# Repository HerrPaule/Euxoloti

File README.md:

# Euxoloti
Euxoloti is a project to use the great Axoloti core in the world of Eurorack. 

The project is fully open and released under CC-BY-SA-NC

Further deatils about functions and order, check http://irieelectronics.de/euxoloti
and the Axoloti Forum: http://community.axoloti.com/t/euxoloti-for-axoloti-eurorack-module/

A great detailed build step by step instruction by FMA from the Axoloti Forum (work in progress): https://docs.google.com/document/d/1Rx9O_k-dUJQDzONVk0AzewmyFckbQyXHiNsPy8fmUj8/edit

AXOLOTI: http://axoloti.be
<br>
Book about the Axoloti: https://leanpub.com/getting-started-with-axoloti

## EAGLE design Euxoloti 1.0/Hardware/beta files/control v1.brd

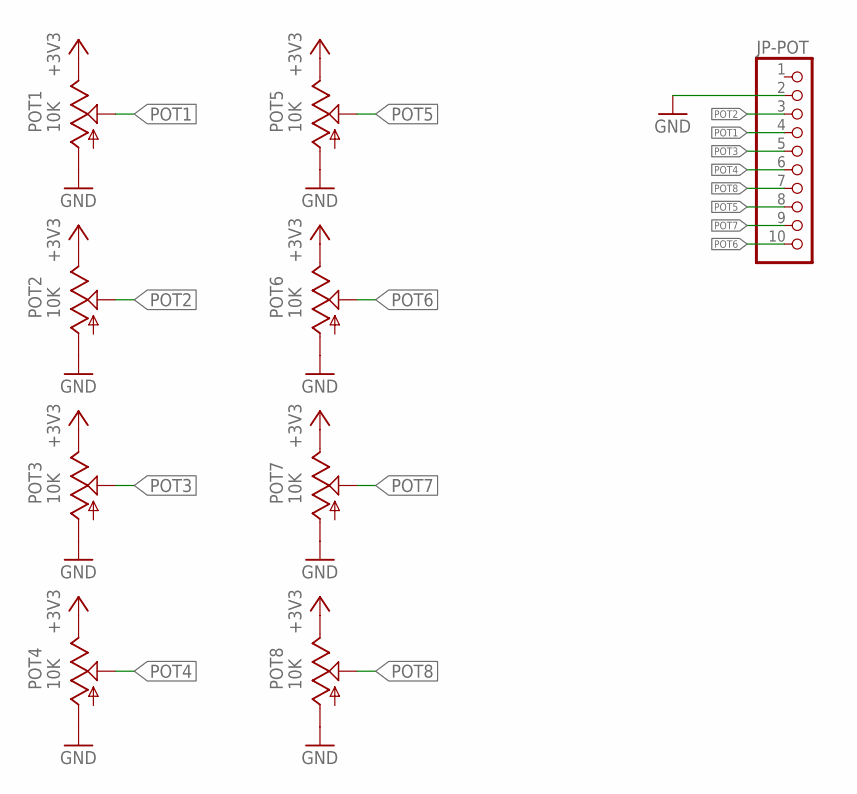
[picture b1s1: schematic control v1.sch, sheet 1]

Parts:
JP-POT: PINHD-1X10_2.54; 1X10
POT1, POT2, POT3, POT4, POT5, POT6, POT7, POT8: 10K; 9MM_SNAP-IN_POT

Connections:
+3V3: POT1.3 (E), POT2.3 (E), POT3.3 (E), POT4.3 (E), POT5.3 (E), POT6.3 (E), POT7.3 (E), POT8.3 (E); also elsewhere on the board
GND: JP-POT.2, POT1.1 (A), POT2.1 (A), POT3.1 (A), POT4.1 (A), POT5.1 (A), POT6.1 (A), POT7.1 (A), POT8.1 (A); also elsewhere on the board
POT1: JP-POT.4, POT1.2 (S)
POT2: JP-POT.3, POT2.2 (S)
POT3: JP-POT.5, POT3.2 (S)
POT4: JP-POT.6, POT4.2 (S)
POT5: JP-POT.8, POT5.2 (S)
POT6: JP-POT.10, POT6.2 (S)
POT7: JP-POT.9, POT7.2 (S)
POT8: JP-POT.7, POT8.2 (S)

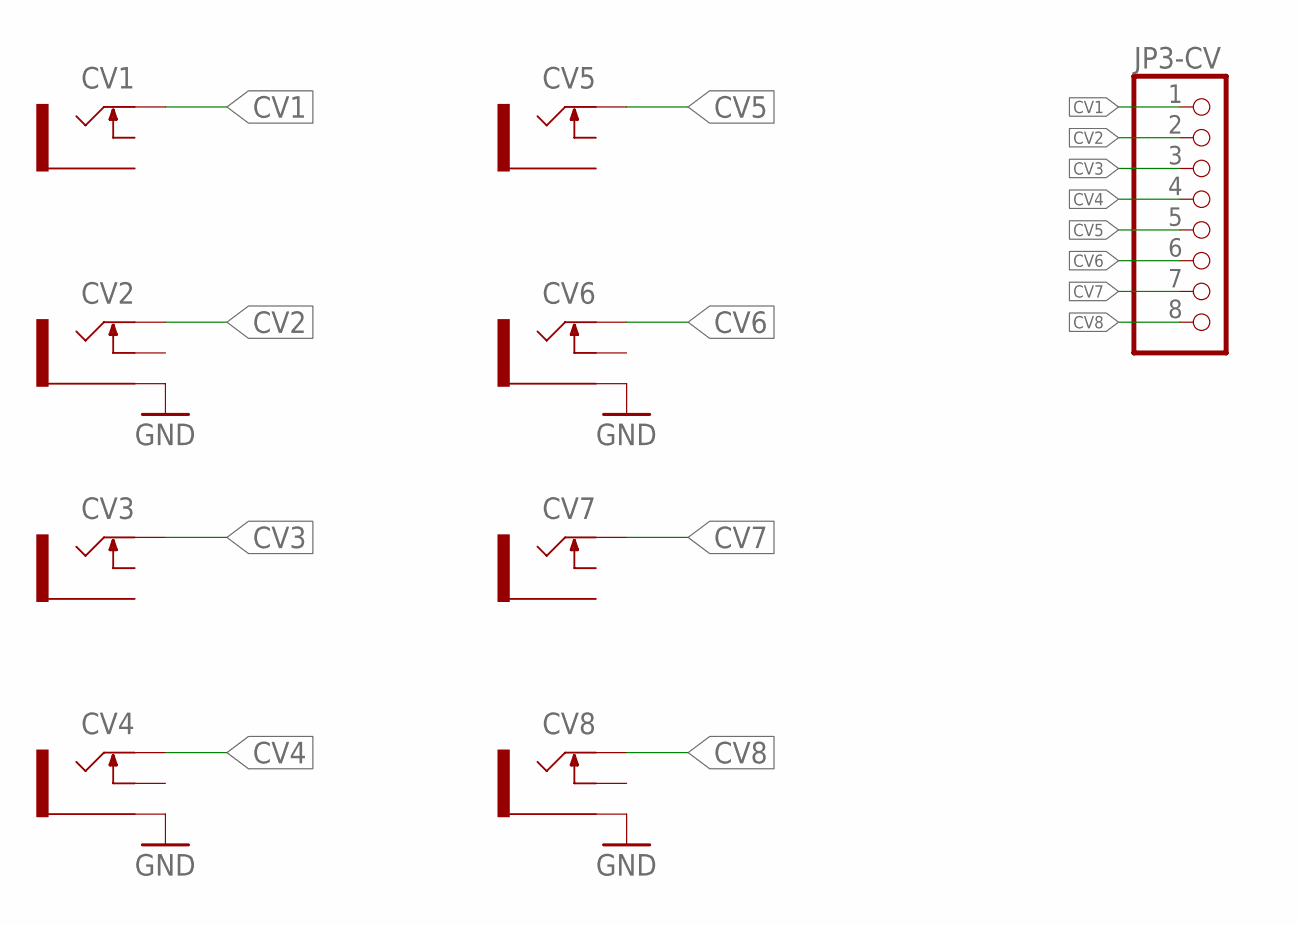
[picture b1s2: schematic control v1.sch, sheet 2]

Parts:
CV1, CV2, CV3, CV4, CV5, CV6, CV7, CV8: THONKICONNNEW; WQP-PJ301M-12_JACK
JP3-CV: PINHD-1X8; 1X08

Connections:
CV1: CV1.P$1_TIP, JP3-CV.1
CV2: CV2.P$1_TIP (TIP), JP3-CV.2
CV3: CV3.P$1_TIP, JP3-CV.3
CV4: CV4.P$1_TIP (TIP), JP3-CV.4
CV5: CV5.P$1_TIP, JP3-CV.5
CV6: CV6.P$1_TIP (TIP), JP3-CV.6
CV7: CV7.P$1_TIP, JP3-CV.7
CV8: CV8.P$1_TIP (TIP), JP3-CV.8
GND: CV2.P$3_SLEEVE (SLEEVE), CV4.P$3_SLEEVE (SLEEVE), CV6.P$3_SLEEVE (SLEEVE), CV8.P$3_SLEEVE (SLEEVE); also elsewhere on the board

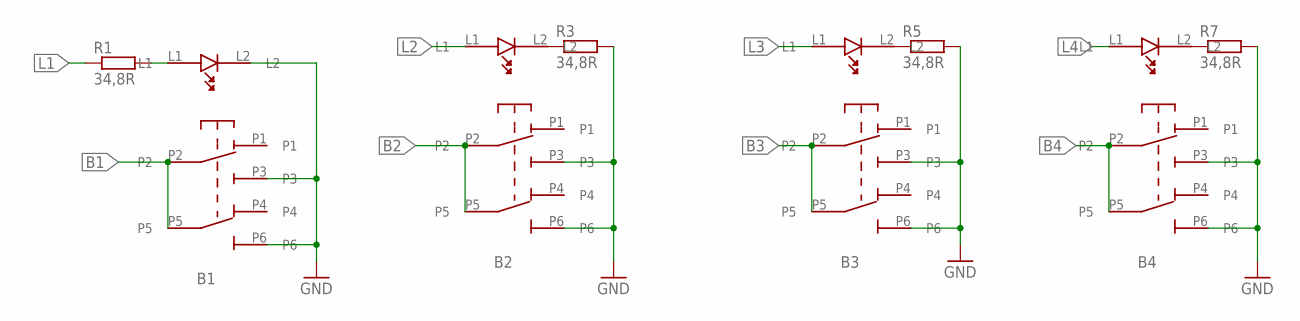
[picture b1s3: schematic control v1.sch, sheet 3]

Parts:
B1, B2, B3, B4: LP4OA1PBCTG; LP4OA1PBCT
R1, R3, R5, R7: 34,8R; 0207/7

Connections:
B1: B1.P2, B1.P5; also elsewhere on the board
B2: B2.P2, B2.P5; also elsewhere on the board
B3: B3.P2, B3.P5; also elsewhere on the board
B4: B4.P2, B4.P5; also elsewhere on the board
GND: B1.L2, B1.P3, B1.P6, B2.P3, B2.P6, B3.P3, B3.P6, B4.P3, B4.P6, R3.2, R5.2, R7.2; also elsewhere on the board
L1: R1.1; also elsewhere on the board
L2: B2.L1; also elsewhere on the board
L3: B3.L1; also elsewhere on the board
L4: B4.L1; also elsewhere on the board
unnamed: B2.L2, R3.1
unnamed: B3.L2, R5.1
unnamed: B1.L1, R1.2
unnamed: B4.L2, R7.1

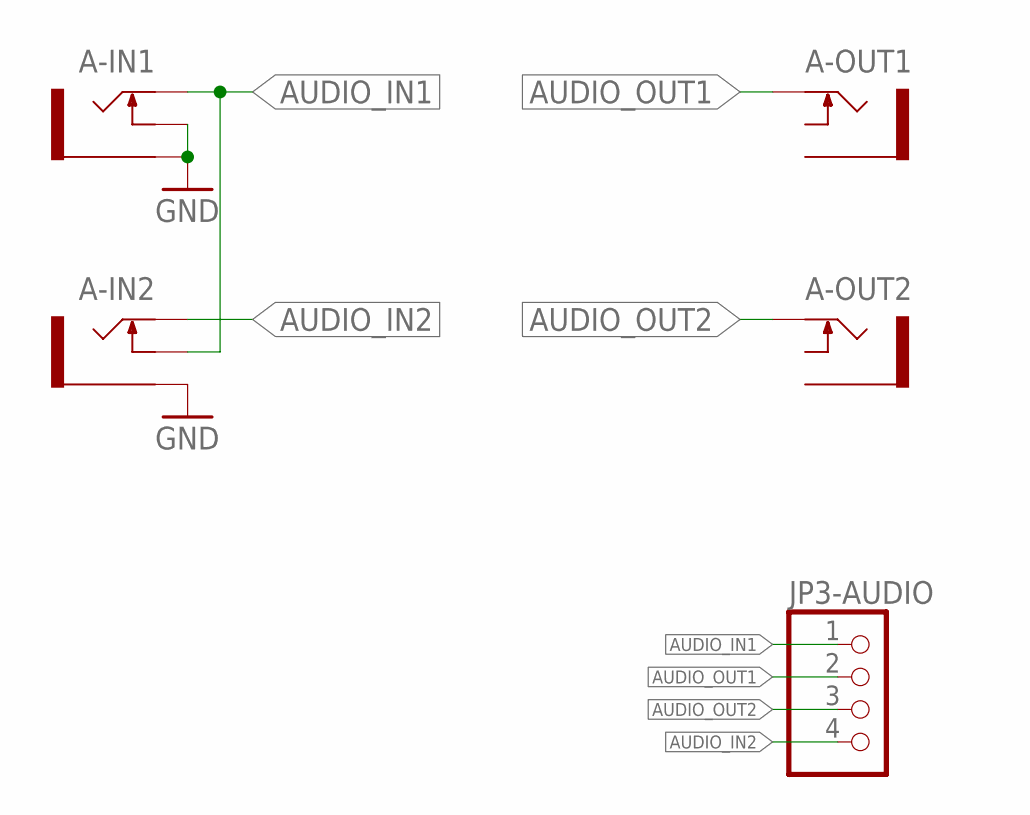
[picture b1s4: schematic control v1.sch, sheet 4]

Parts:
A-IN1, A-IN2: THONKICONNNEW; WQP-PJ301M-12_JACK
A-OUT1, A-OUT2: THONKICONNNEW; WQP-PJ301M-12_JACK
JP3-AUDIO: PINHD-1X4; 1X04

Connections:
AUDIO_IN1: A-IN1.P$1_TIP (TIP), A-IN2.P$2_SWITCH (SWITCH), JP3-AUDIO.1
AUDIO_IN2: A-IN2.P$1_TIP (TIP), JP3-AUDIO.4
AUDIO_OUT1: A-OUT1.P$1_TIP, JP3-AUDIO.2
AUDIO_OUT2: A-OUT2.P$1_TIP, JP3-AUDIO.3
GND: A-IN1.P$2_SWITCH (SWITCH), A-IN1.P$3_SLEEVE (SLEEVE), A-IN2.P$3_SLEEVE (SLEEVE); also elsewhere on the board

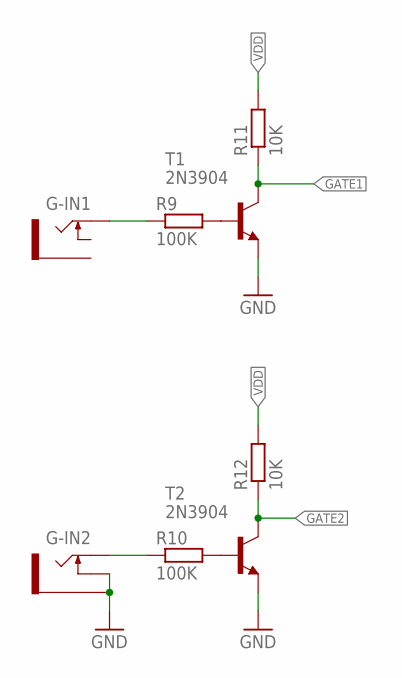
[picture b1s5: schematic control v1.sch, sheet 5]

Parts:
G-IN1, G-IN2: THONKICONNNEW; WQP-PJ301M-12_JACK
R9, R10: 100K; 0207/7
R11, R12: 10K; 0207/7
T1, T2: 2N3904; TO92

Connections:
GATE1: R11.1, T1.1 (C); also elsewhere on the board
GATE2: R12.1, T2.1 (C); also elsewhere on the board
GND: G-IN2.P$2_SWITCH (SWITCH), G-IN2.P$3_SLEEVE (SLEEVE), T1.3 (E), T2.3 (E); also elsewhere on the board
unnamed: G-IN1.P$1_TIP, R9.1
unnamed: G-IN2.P$1_TIP (TIP), R10.1
unnamed: R9.2, T1.2 (B)
unnamed: R10.2, T2.2 (B)
VDD: R11.2, R12.2; also elsewhere on the board

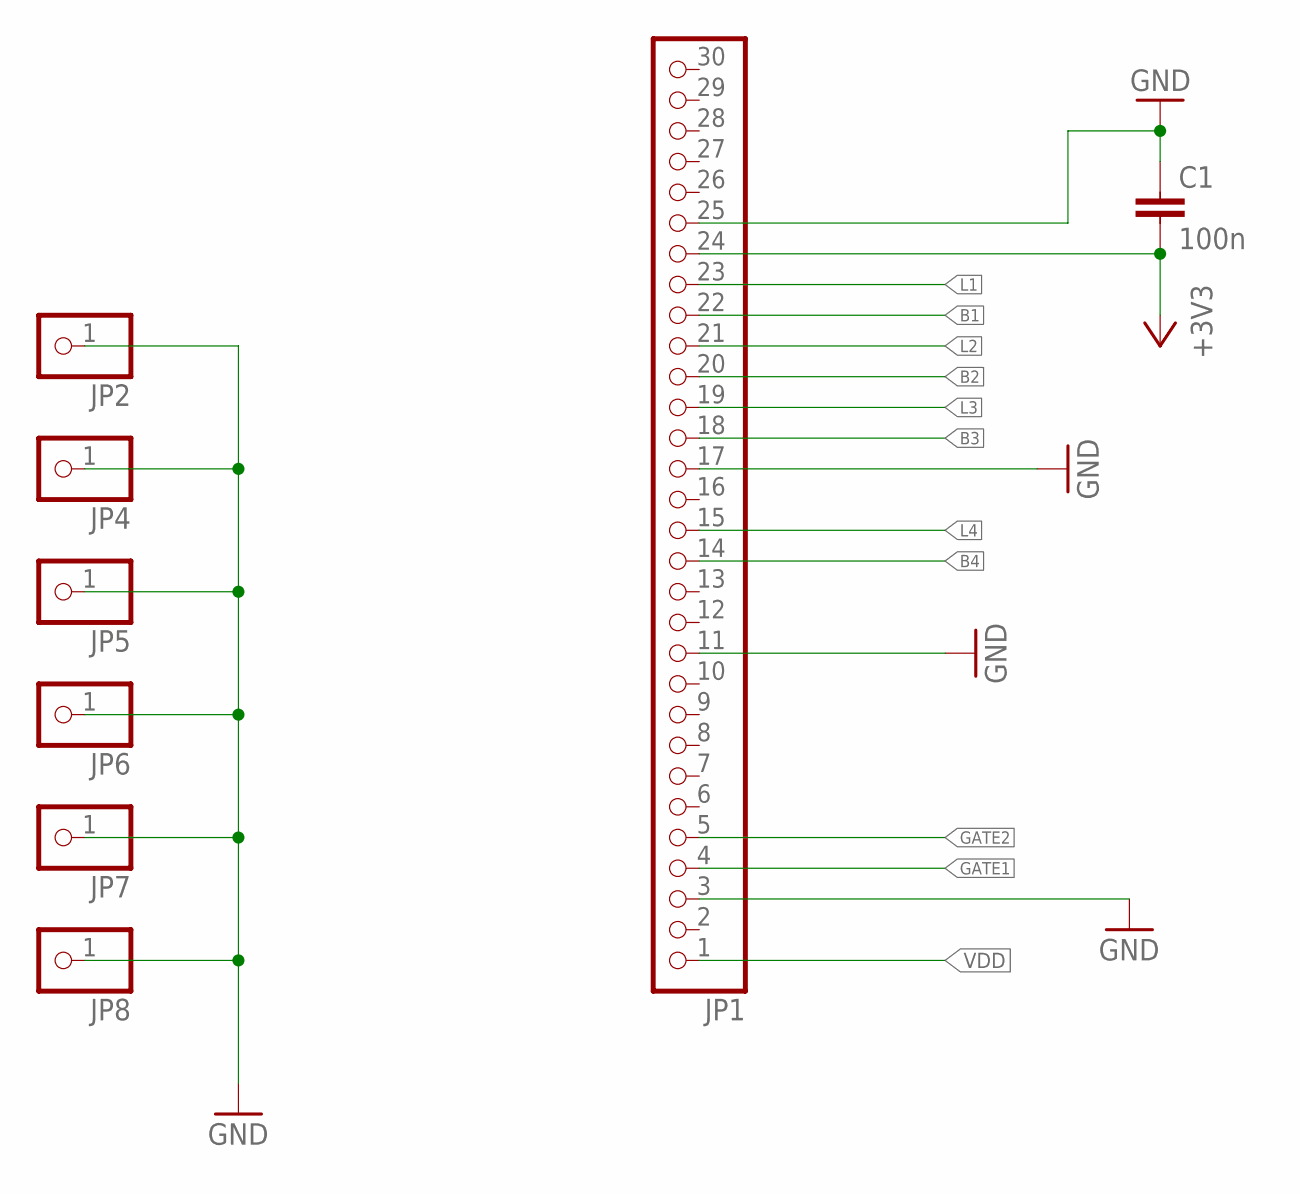
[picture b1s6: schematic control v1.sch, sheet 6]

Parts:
C1: 100n; C025-025X050
JP1: PINHD-1X30; 1X30
JP2, JP4, JP5, JP6, JP7, JP8: PINHD-1X1; 1X01

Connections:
+3V3: C1.2, JP1.24; also elsewhere on the board
B1: JP1.22; also elsewhere on the board
B2: JP1.20; also elsewhere on the board
B3: JP1.18; also elsewhere on the board
B4: JP1.14; also elsewhere on the board
GATE1: JP1.4; also elsewhere on the board
GATE2: JP1.5; also elsewhere on the board
GND: C1.1, JP1.3, JP1.11, JP1.17, JP1.25, JP2.1, JP4.1, JP5.1, JP6.1, JP7.1, JP8.1; also elsewhere on the board
L1: JP1.23; also elsewhere on the board
L2: JP1.21; also elsewhere on the board
L3: JP1.19; also elsewhere on the board
L4: JP1.15; also elsewhere on the board
VDD: JP1.1; also elsewhere on the board

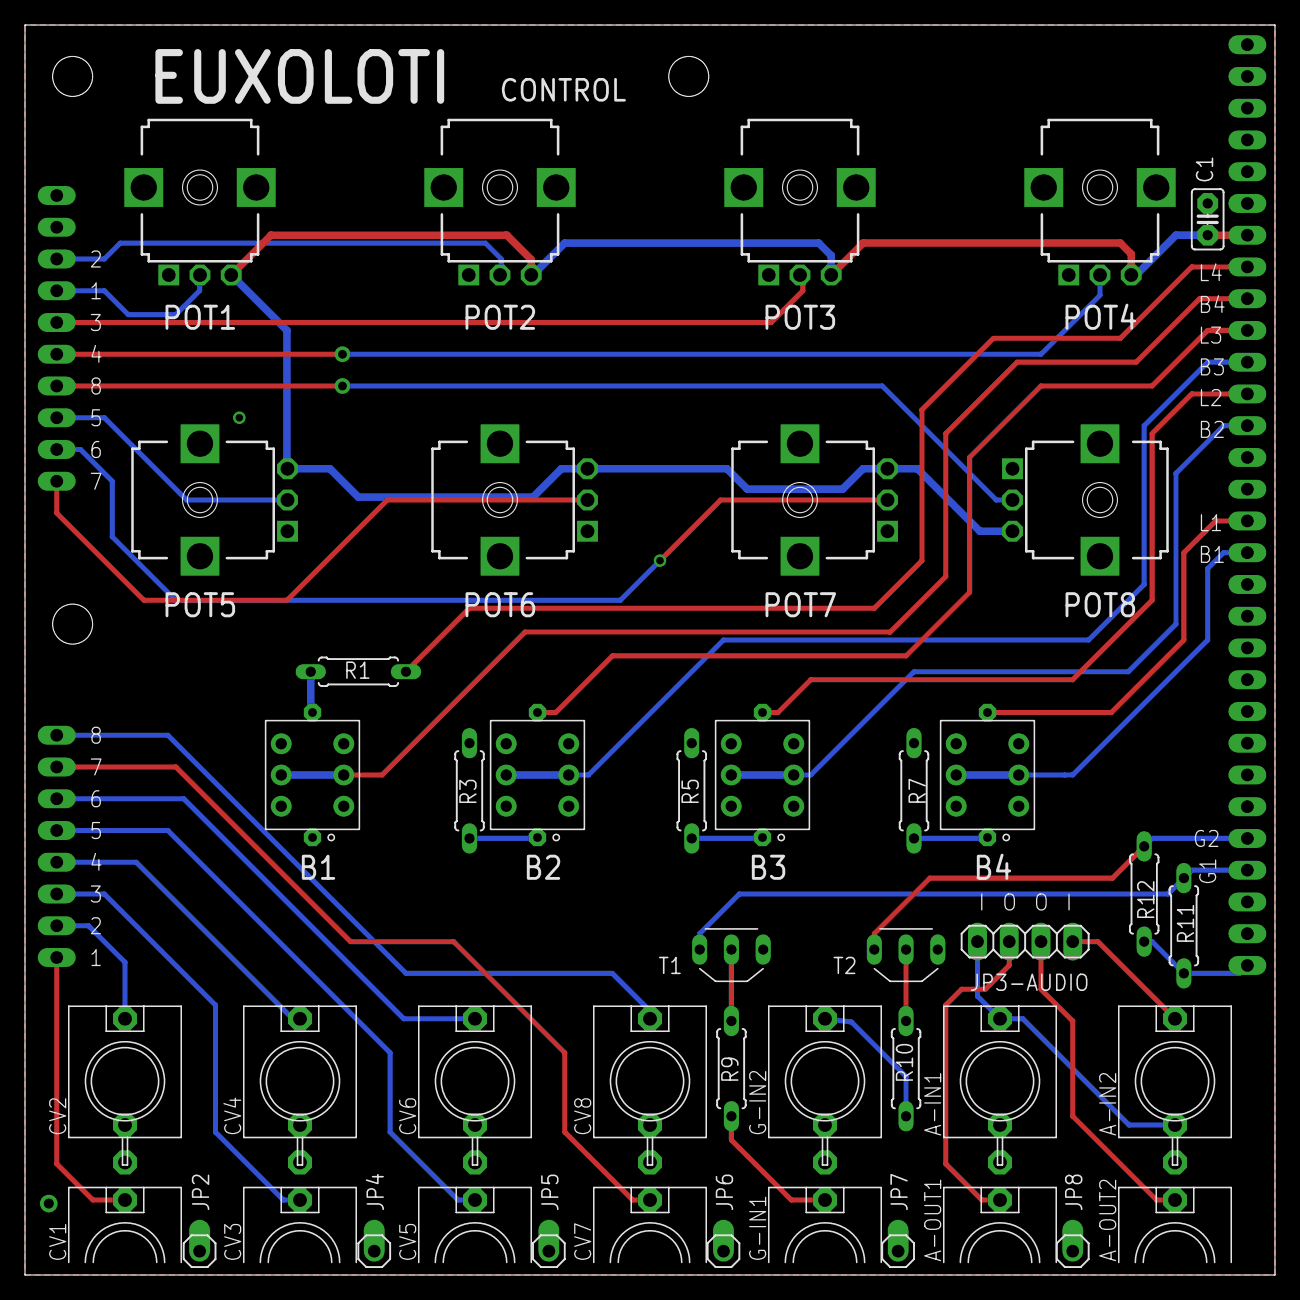
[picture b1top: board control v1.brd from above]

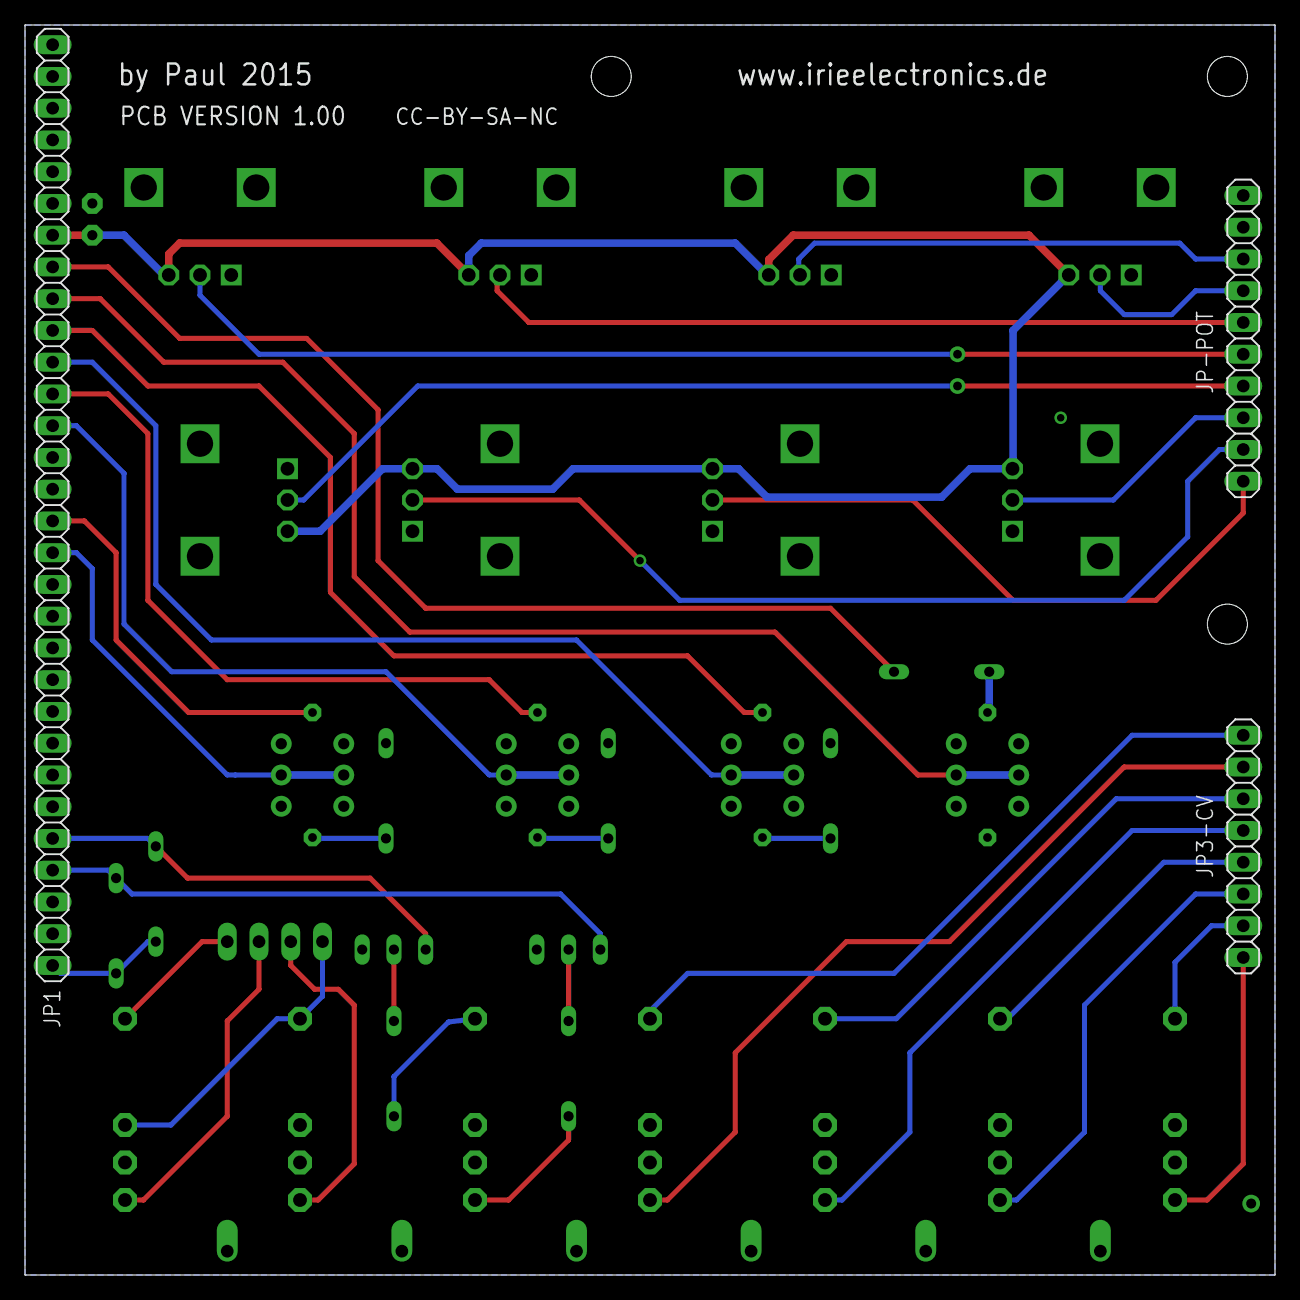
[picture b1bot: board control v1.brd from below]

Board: 4 copper layers, 100.0 x 100.0 mm, 47 parts (3 on the bottom side), 41 nets.

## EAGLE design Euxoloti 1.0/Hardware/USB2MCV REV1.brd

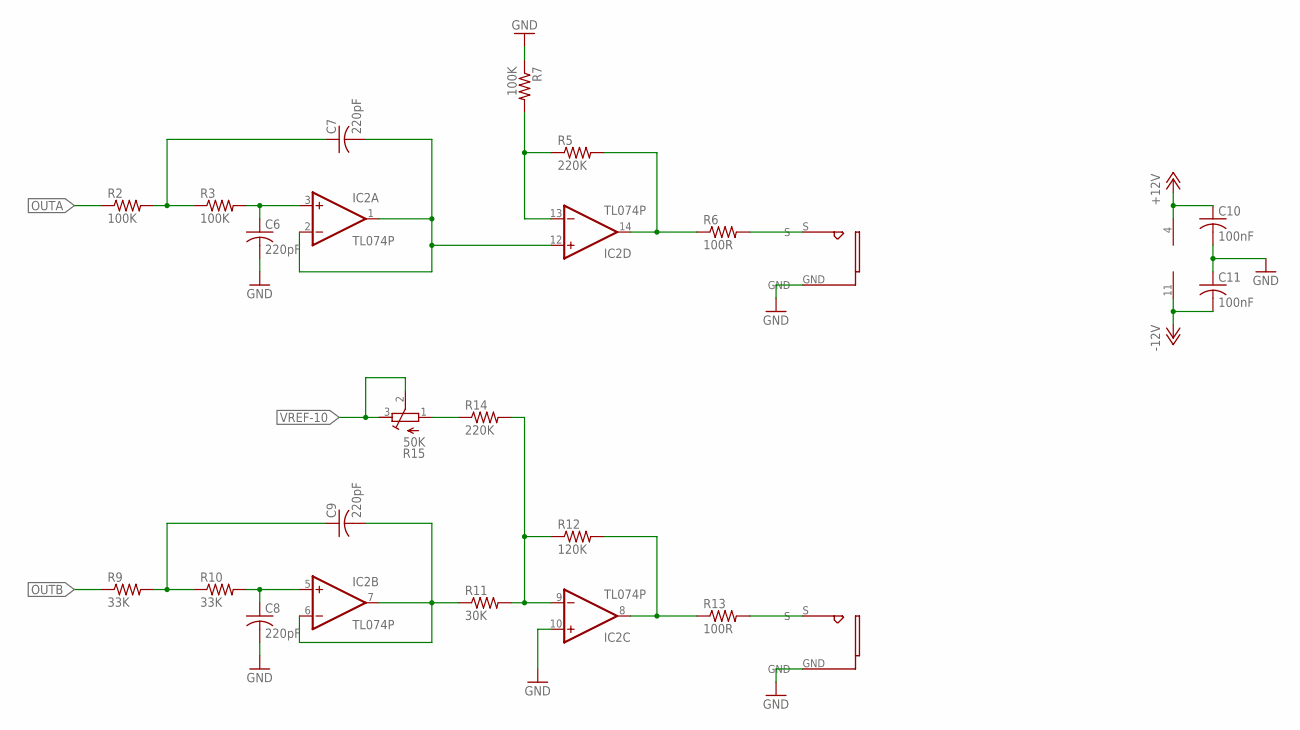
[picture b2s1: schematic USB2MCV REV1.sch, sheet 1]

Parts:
C6, C7, C8, C9: 220pF; C1206K
C10, C11: 100nF; C1206K
IC2: TL074P; DIL14
OUT1, OUT2: PJ302M
R2, R3, R7: 100K; R1206
R5, R14: 220K; R1206
R6, R13: 100R; R1206
R9, R10: 33K; R1206
R11: 30K; R1206
R12: 120K; R1206
R15: 50K; RTRIM64Y

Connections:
+12V: C10.1, IC2.4 (V+); also elsewhere on the board
-12V: C11.2, IC2.11 (V-); also elsewhere on the board
GND: C6.2, C8.2, C10.2, C11.1, IC2.10 (+IN), OUT1.GND, OUT2.GND, R7.1; also elsewhere on the board
unnamed: C6.1, IC2.3 (+IN), R3.2
unnamed: C7.1, R2.2, R3.1
unnamed: IC2.13 (-IN), R5.1, R7.2
unnamed: IC2.14 (OUT), R5.2, R6.1
unnamed: C9.2, IC2.6 (-IN), IC2.7 (OUT), R11.1
unnamed: C8.1, IC2.5 (+IN), R10.2
unnamed: C9.1, R9.2, R10.1
unnamed: IC2.9 (-IN), R11.2, R12.1, R14.2
unnamed: IC2.8 (OUT), R12.2, R13.1
unnamed: R14.1, R15.1 (E)
unnamed: C7.2, IC2.1 (OUT), IC2.2 (-IN), IC2.12 (+IN)
OUT1: OUT1.S, R6.2
OUT2: OUT2.S, R13.2
OUTA: R2.1; also elsewhere on the board
OUTB: R9.1; also elsewhere on the board
VREF-10: R15.2 (S), R15.3 (A); also elsewhere on the board

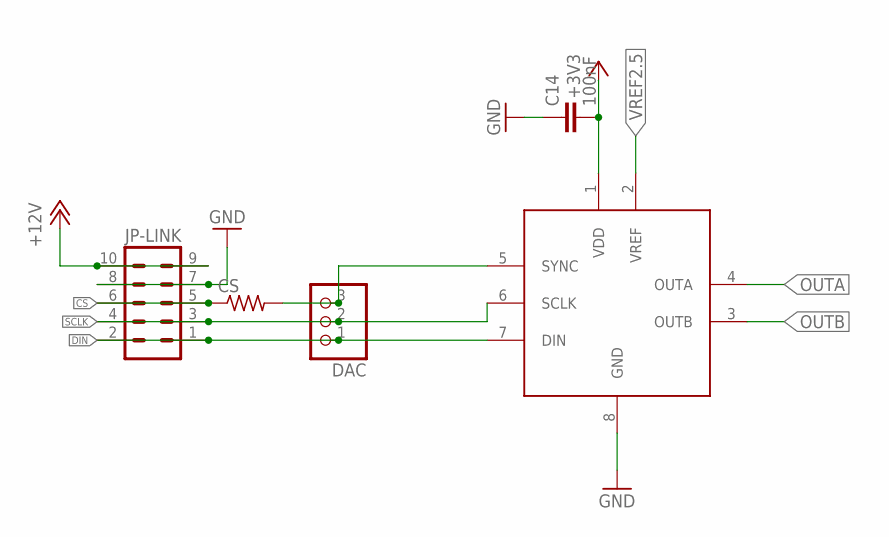
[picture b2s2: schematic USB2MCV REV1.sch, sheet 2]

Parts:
C14: 100nF; C1206K
CS: R-US_R0402; R0402
DAC: PINHD-1X3_2.54; 1X03
IC5: DAC8552; MSOP-8
JP-LINK: ML10

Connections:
+3V3: C14.2, IC5.1 (VDD); also elsewhere on the board
+12V: JP-LINK.9, JP-LINK.10; also elsewhere on the board
CS: CS.1, JP-LINK.5, JP-LINK.6
DIN: DAC.1, IC5.7 (DIN), JP-LINK.1, JP-LINK.2
GND: C14.1, IC5.8 (GND), JP-LINK.7, JP-LINK.8; also elsewhere on the board
OUTA: IC5.4 (OUTA); also elsewhere on the board
OUTB: IC5.3 (OUTB); also elsewhere on the board
SCLK: DAC.2, IC5.6 (SCLK), JP-LINK.3, JP-LINK.4
SYNC: CS.2, DAC.3, IC5.5 (SYNC)
VREF2.5: IC5.2 (VREF); also elsewhere on the board

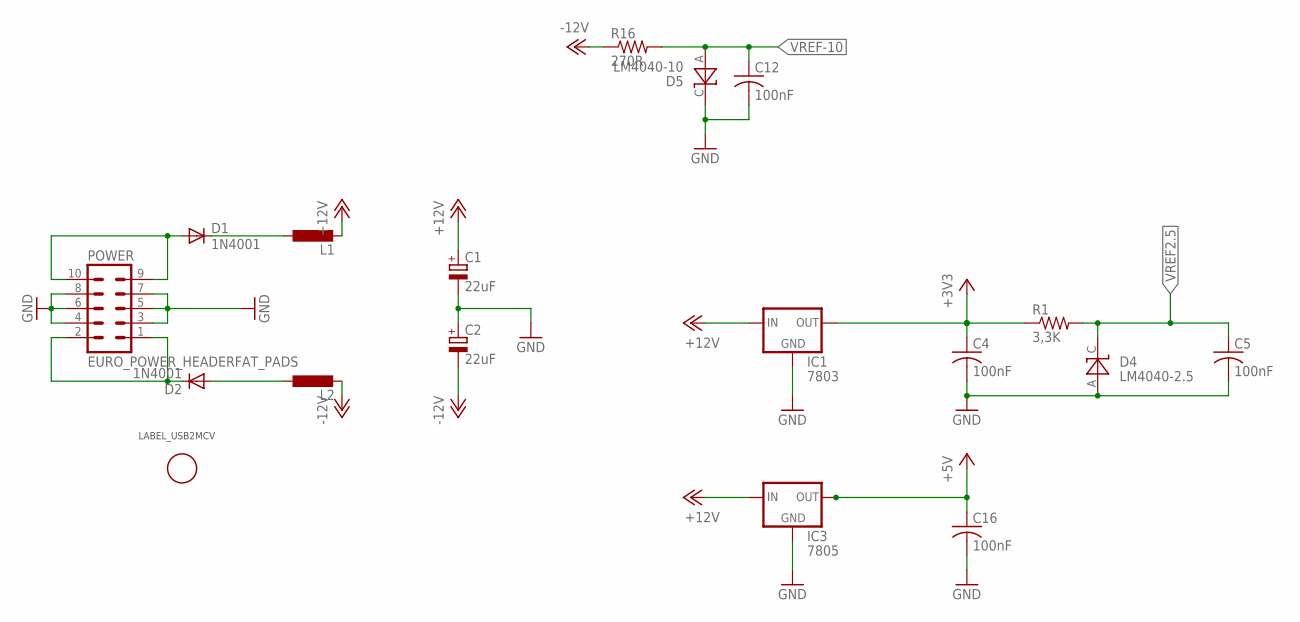
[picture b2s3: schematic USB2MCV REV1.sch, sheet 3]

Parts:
C1, C2: 22uF; E2-5
C4, C5, C12, C16: 100nF; C1206K
D1, D2: 1N4001; DO41-10
D4: LM4040-2.5; TO-92
D5: LM4040-10; TO-92
IC1: 7803; 78LXX
IC3: 7805; 78LXX
L1, L2: L-EU0207/10; 0207/10
POWER: EURO_POWER_HEADERFAT_PADS; EURO_PWR_HEADER_FAT
R1: 3,3K; R1206
R16: 270R; R1206
U$1: LABEL_USB2MCV; LABEL_USB2DAC

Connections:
+3V3: C4.1, IC1.OUT, R1.1; also elsewhere on the board
+5V: C16.1, IC3.OUT; also elsewhere on the board
+12V: C1.+, IC1.IN, IC3.IN, L1.2; also elsewhere on the board
-12V: C2.-, L2.2, R16.1; also elsewhere on the board
GND: C1.-, C2.+, C4.2, C5.2, C12.2, C16.2, D4.A, D5.C, IC1.GND, IC3.GND, POWER.3, POWER.4, POWER.5, POWER.6, POWER.7, POWER.8; also elsewhere on the board
unnamed: D2.C, POWER.1, POWER.2
unnamed: D1.A, POWER.9, POWER.10
unnamed: D2.A, L2.1
unnamed: D1.C, L1.1
VREF2.5: C5.1, D4.C, R1.2; also elsewhere on the board
VREF-10: C12.1, D5.A, R16.2; also elsewhere on the board

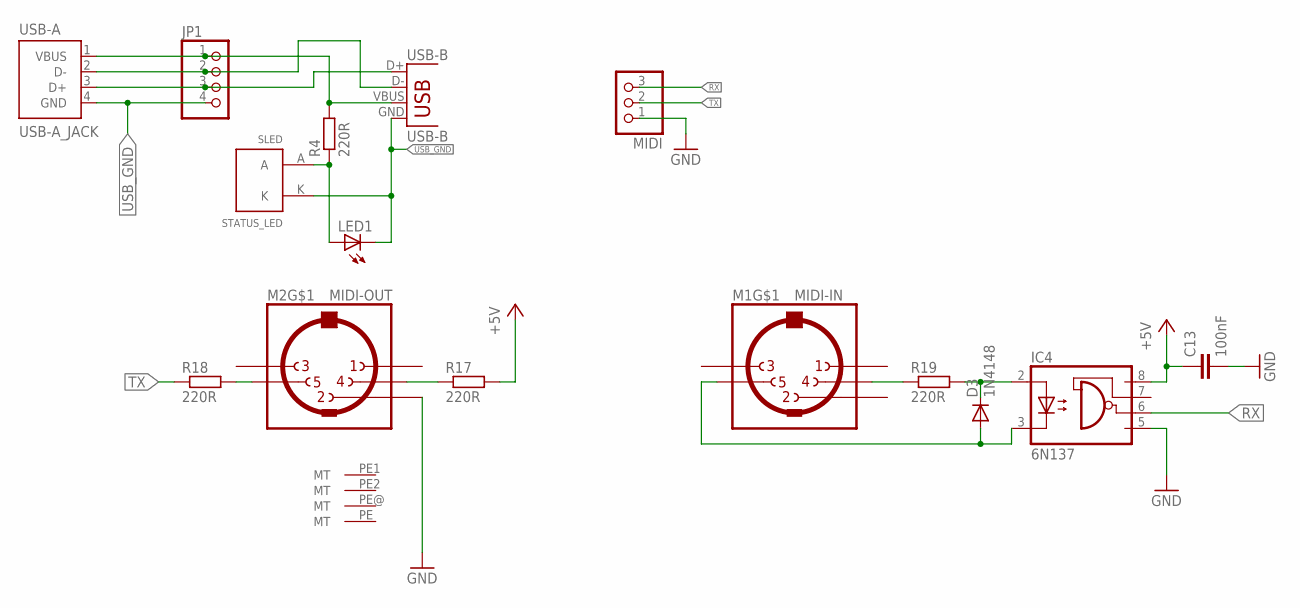
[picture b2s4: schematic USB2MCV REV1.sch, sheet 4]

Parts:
C13: 100nF; C1206K
D3: 1N4148; DO35-7
IC4: 6N137; DIL08
JP1: PINHD-1X4_2.54; 1X04
LED1: LED1206; LED-1206
M1: MIDI-IN; CP-2350
M2: MIDI-OUT; CP-2350
MIDI: PINHD-1X3_2.54; 1X03
R4, R17, R18, R19: 220R; R1206@1
SLED: STATUS_LED; STAUS-LED(DIP)
USB-A: USB-A_JACK; USB-A
USB-B: USB-B; USB-B-PTH

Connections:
+5V: C13.1, IC4.8 (VCC), R17.2; also elsewhere on the board
D+: JP1.3, USB-A.3 (D+), USB-B.D+
D-: JP1.2, USB-A.2 (D-), USB-B.D-
GND: C13.2, IC4.5 (GND), M2.2, MIDI.1; also elsewhere on the board
unnamed: LED1.A, R4.1, SLED.A
unnamed: D3.C, IC4.2 (A), R19.2
unnamed: M2.5, R18.2
unnamed: JP1.1, R4.2, USB-A.1 (VBUS), USB-B.VBUS
unnamed: M2.4, R17.1
unnamed: M1.4, R19.1
unnamed: D3.A, IC4.3 (C), M1.5
RX: IC4.6 (VO), MIDI.3
TX: MIDI.2, R18.1
USB_GND: JP1.4, LED1.C, SLED.K, USB-A.4 (GND), USB-B.GND

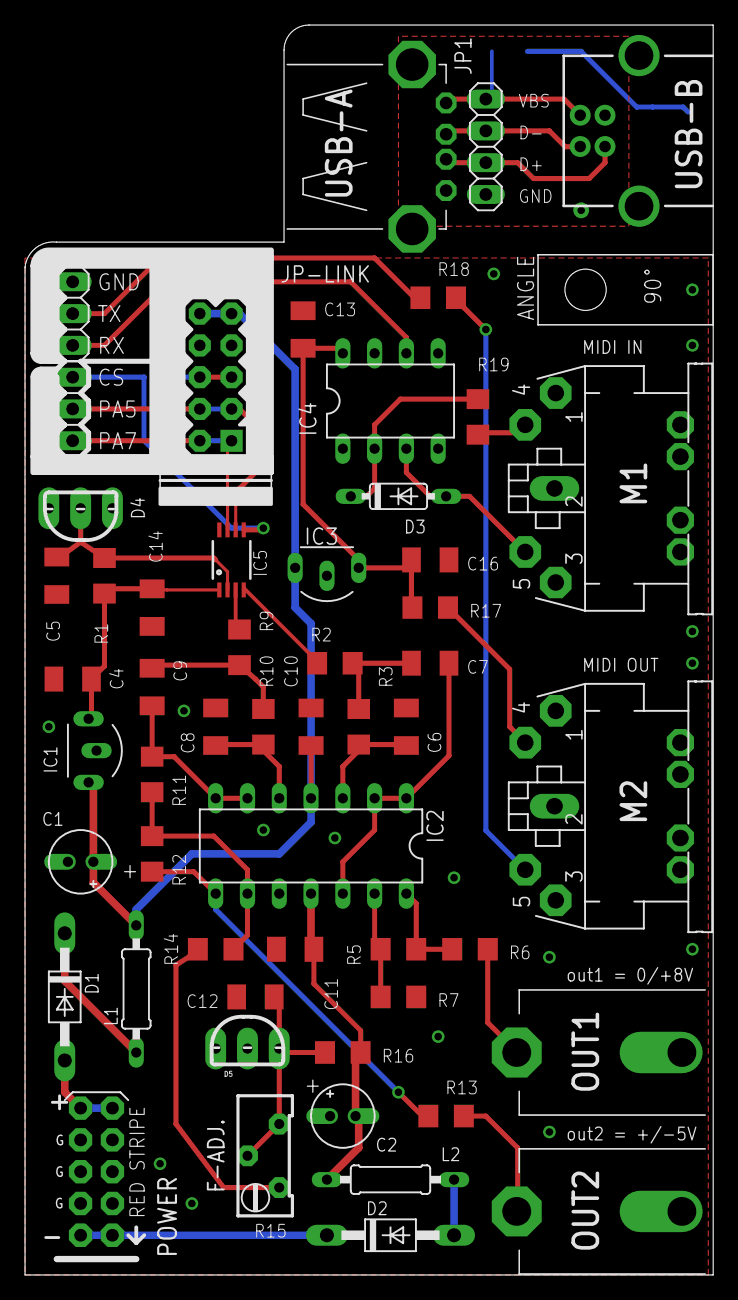
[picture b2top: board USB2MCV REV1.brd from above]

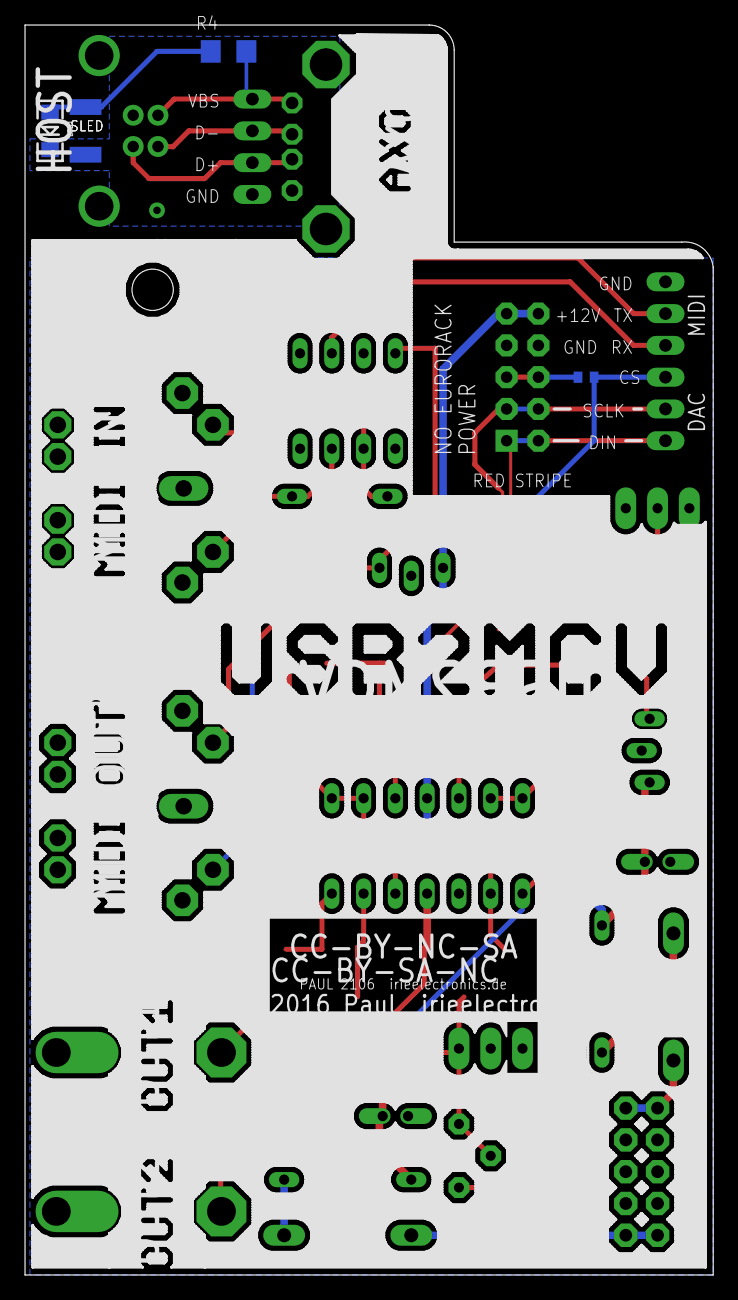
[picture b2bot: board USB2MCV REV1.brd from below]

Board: 4 copper layers, 55.0 x 99.9 mm, 60 parts (4 on the bottom side), 42 nets.

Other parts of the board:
U$2: WINKEL; WINKEL90°

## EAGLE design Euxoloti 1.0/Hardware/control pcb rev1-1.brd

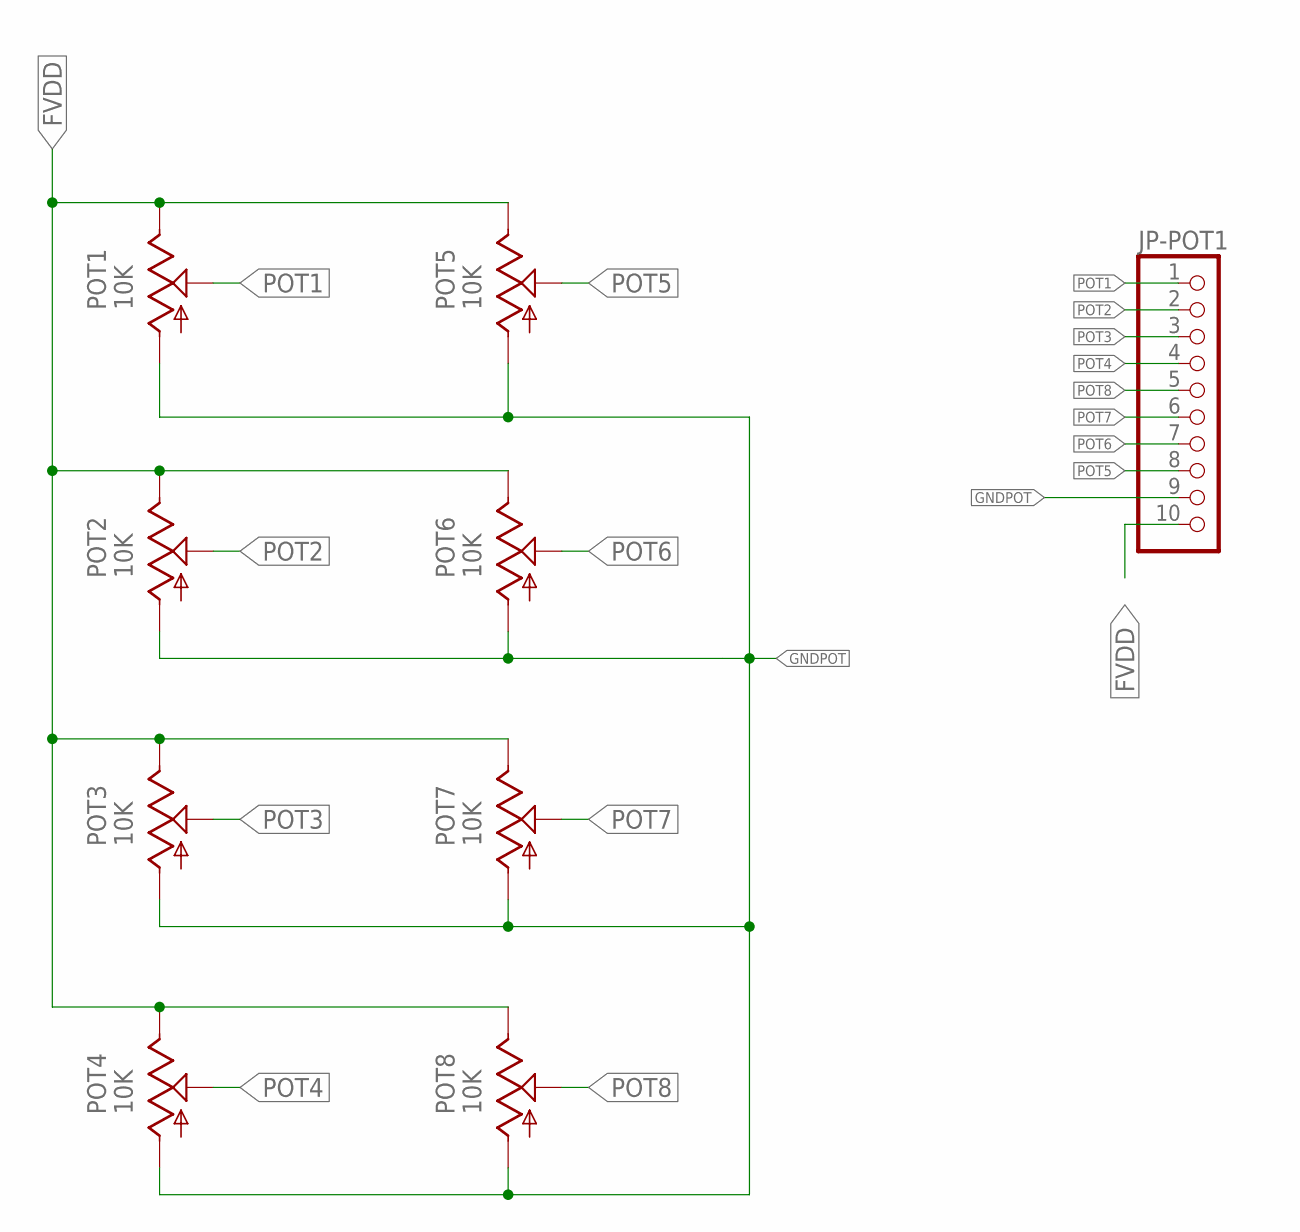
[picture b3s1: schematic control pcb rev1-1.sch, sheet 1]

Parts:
JP-POT1: PINHD-1X10_2.54; 1X10
POT1, POT2, POT3, POT4, POT5, POT6, POT7, POT8: 10K; 9MM_SNAP-IN_POT

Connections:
FVDD: JP-POT1.10, POT1.3 (E), POT2.3 (E), POT3.3 (E), POT4.3 (E), POT5.3 (E), POT6.3 (E), POT7.3 (E), POT8.3 (E)
GNDPOT: JP-POT1.9, POT1.1 (A), POT2.1 (A), POT3.1 (A), POT4.1 (A), POT5.1 (A), POT6.1 (A), POT7.1 (A), POT8.1 (A)
POT1: JP-POT1.1, POT1.2 (S)
POT2: JP-POT1.2, POT2.2 (S)
POT3: JP-POT1.3, POT3.2 (S)
POT4: JP-POT1.4, POT4.2 (S)
POT5: JP-POT1.8, POT5.2 (S)
POT6: JP-POT1.7, POT6.2 (S)
POT7: JP-POT1.6, POT7.2 (S)
POT8: JP-POT1.5, POT8.2 (S)

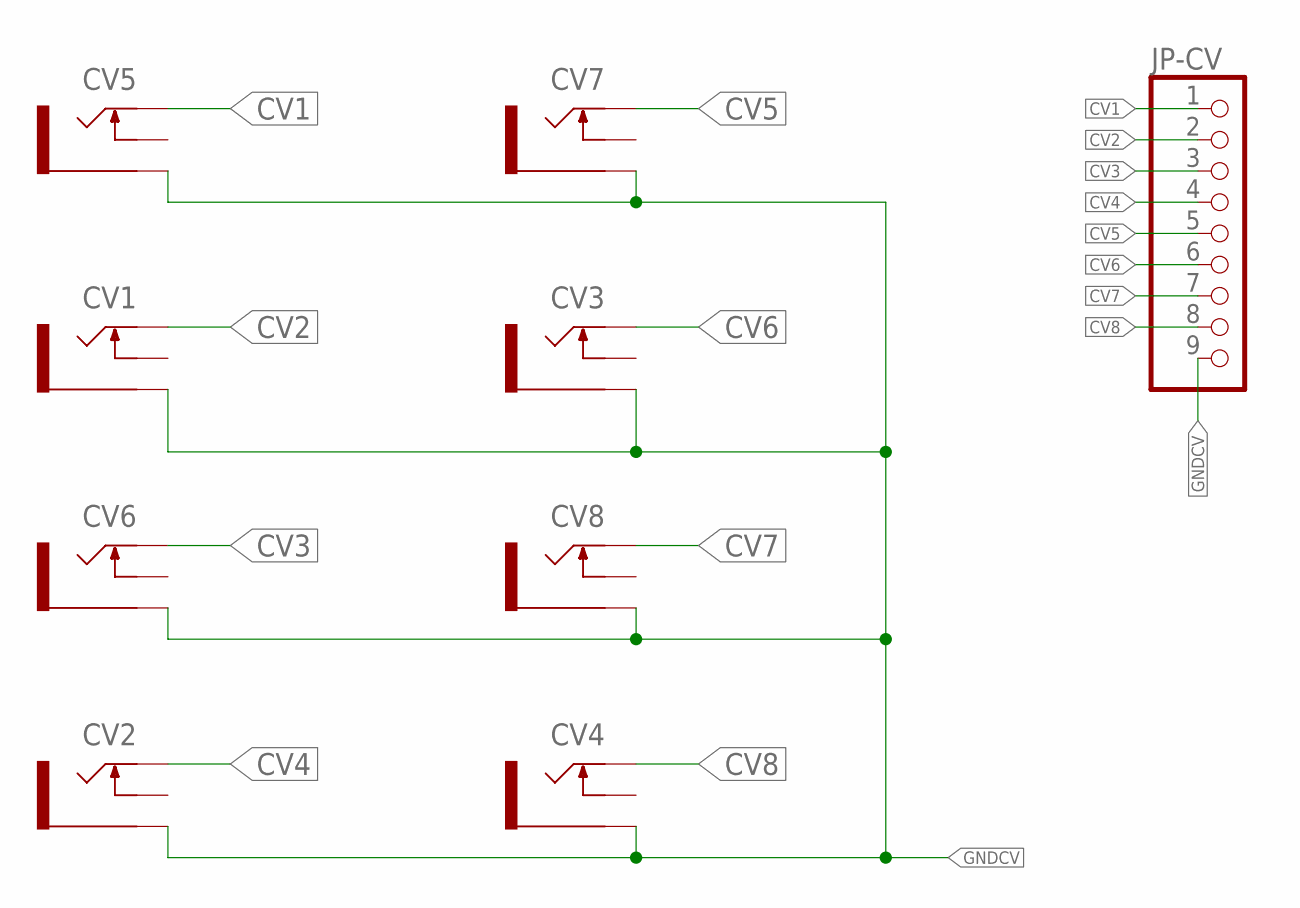
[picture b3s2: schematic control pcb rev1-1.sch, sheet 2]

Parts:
CV1, CV2, CV3, CV4, CV5, CV6, CV7, CV8: THONKICONNNEW; WQP-PJ301M-12_JACK
JP-CV: PINHD-1X9_2.54; 1X09

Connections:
CV1: CV5.P$1_TIP (TIP), JP-CV.1
CV2: CV1.P$1_TIP (TIP), JP-CV.2
CV3: CV6.P$1_TIP (TIP), JP-CV.3
CV4: CV2.P$1_TIP (TIP), JP-CV.4
CV5: CV7.P$1_TIP (TIP), JP-CV.5
CV6: CV3.P$1_TIP (TIP), JP-CV.6
CV7: CV8.P$1_TIP (TIP), JP-CV.7
CV8: CV4.P$1_TIP (TIP), JP-CV.8
GNDCV: CV1.P$3_SLEEVE (SLEEVE), CV2.P$3_SLEEVE (SLEEVE), CV3.P$3_SLEEVE (SLEEVE), CV4.P$3_SLEEVE (SLEEVE), CV5.P$3_SLEEVE (SLEEVE), CV6.P$3_SLEEVE (SLEEVE), CV7.P$3_SLEEVE (SLEEVE), CV8.P$3_SLEEVE (SLEEVE), JP-CV.9; also elsewhere on the board

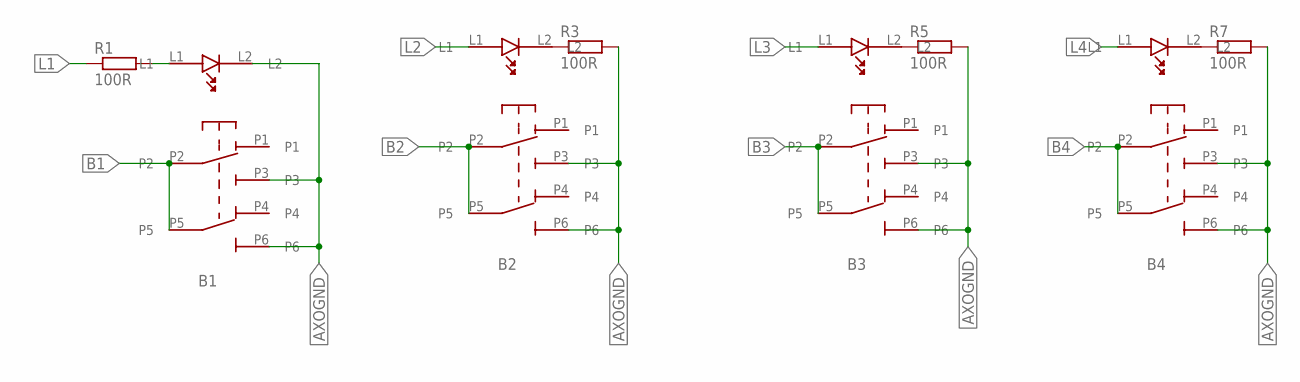
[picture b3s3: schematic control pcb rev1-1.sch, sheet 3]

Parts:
B1, B2, B3, B4: LP4OA1PBCTG/D6; LP4OA1PBCT
R1, R3, R5, R7: 100R; 0207/7

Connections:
AXOGND: B1.L2, B1.P3, B1.P6, B2.P3, B2.P6, B3.P3, B3.P6, B4.P3, B4.P6, R3.2, R5.2, R7.2; also elsewhere on the board
B1: B1.P2, B1.P5; also elsewhere on the board
B2: B2.P2, B2.P5; also elsewhere on the board
B3: B3.P2, B3.P5; also elsewhere on the board
B4: B4.P2, B4.P5; also elsewhere on the board
L1: R1.1; also elsewhere on the board
L2: B2.L1; also elsewhere on the board
L3: B3.L1; also elsewhere on the board
L4: B4.L1; also elsewhere on the board
unnamed: B2.L2, R3.1
unnamed: B3.L2, R5.1
unnamed: B1.L1, R1.2
unnamed: B4.L2, R7.1

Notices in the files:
Euxoloti 1.0/Hardware/USB2MCV REV1.brd:
CC-BY-NC-SA
parts and their libraries:
SparkFun-Connectors: Licensing: Creative Commons ShareAlike 4.0 International - https://creativecommons.org/licenses/by-sa/4.0
SparkFun-LED: Licensing: CC v3.0 Share-Alike You are welcome to use this library for commercial purposes.
